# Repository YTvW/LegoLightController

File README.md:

# QBee LED Controller

A LEGO-stud-compatible LED controller board (Rev 1.0) built around the ATSAMD11C14A,
powered over USB-C. It drives up to two WS2812B (NeoPixel) strips and three
single-color LED channels.

## Hardware overview

| Part | Function |
|---|---|
| U1 — ATSAMD11C14A (SOIC-14) | MCU, 16KB flash / 4KB RAM, native USB |
| U2 — AP2111H-3.3 | 3.3V LDO for the MCU |
| P1 — USB-C (USB4110) | Power (5V) + USB 2.0 data; 5.1k CC pulldowns identify the board as a power sink |
| Q1–Q3 — BC847 | Low-side switches for the three LED channels (1k base, 10k pulldown) |
| R10, R11 — 470Ω | Series resistors on the WS2812B data lines |

### Connectors / IO

| Connector | Pads | Signal | MCU pin | Arduino pin |
|---|---|---|---|---|
| J1 | 1: +5V, 2: switched GND | LED1 channel | PA02 | 2 |
| J2 | 1: +5V, 2: switched GND | LED2 channel | PA04 | 4 |
| J3 | 1: +5V, 2: switched GND | LED3 channel | PA05 | 5 |
| J4 | 1: +5V, 2: data, 3: GND | WS2812B strip (DL1) | PA14 | 14 |
| J5 | 1: +5V, 2: data, 3: GND | WS2812B strip (DL2) | PA15 | 15 |
| J7 | 1: 3V3, 2: RESET, 3: SWCLK, 4: SWDIO, 5: NC, 6: GND | SWD programming header (DNP) | PA28/PA30/PA31 | — |
| TP1 | test point | EXT1 spare GPIO | PA08 | 8 |
| TP2 | test point | EXT2 spare GPIO | PA09 | 9 |

The LED channels (J1–J3) switch the LED's ground side through a transistor:
connect an LED (with its own series resistor if needed) between pad 1 (+5V)
and pad 2. A HIGH on the MCU pin turns the channel on.

Notes per pin:

- **PA02 (LED1, pin 2)** has no timer output — hardware PWM is not possible.
  `analogWrite()` on this pin uses the true 10-bit DAC; the transistor makes
  this behave as a crude analog dimmer only. Prefer channels LED2/LED3 for
  smooth PWM dimming.
- **PA04/PA05 (LED2/LED3)** have TC1 waveform outputs (WO0/WO1) — used by
  `pwm_driver` channels 0 and 1.
- **PA14/PA15 (strips)** also carry TC1 outputs; do not `analogWrite()` them.

## Arduino environment setup

1. Install the [Arduino IDE](https://www.arduino.cc/en/software) (2.x).
2. Add the Fab SAM core: **File → Preferences → Additional boards manager URLs**:

   ```
   https://raw.githubusercontent.com/qbolsee/ArduinoCore-fab-sam/master/json/package_Fab_SAM_index.json
   ```

3. **Tools → Board → Boards Manager**, search "Fab SAM", install
   **Fab SAM core for Arduino** (this project was built with 1.12.0).
4. Select **Tools → Board → Fab SAM boards → Generic D11C14A**.

### Board settings (Tools menu)

| Setting | Value | Notes |
|---|---|---|
| Clock Source | `INTERNAL_USB_CALIBRATED_OSCILLATOR` | Crystalless; calibrates 48MHz from USB. Switch to `INTERNAL_OSCILLATOR` if USB is disabled. |
| Bootloader Size | `4KB_BOOTLOADER` | Leaves 12KB for the application |
| Serial Config | `NO_UART_ONE_WIRE_ONE_SPI` | Saves ~1.5KB vs the default; USB `Serial` still works. The hardware UART (`Serial1`) is not wired to anything on this board. |
| USB Config | `CDC_ONLY` | Needed for `Serial` debugging and one-click uploads |
| Float | default | |
| Timer PWM Frequency | default (732.4Hz) | Only affects `analogWrite()` |

### Uploading

Normal uploads go over USB via the SAM-BA bootloader: just press Upload —
the IDE opens the port at 1200 baud to reset the board into the bootloader
automatically (this requires the running sketch to have USB CDC enabled).

If the chip is blank, or the sketch was built without CDC, flash via the SWD
pads (J7) with a CMSIS-DAP programmer and
[edbg](https://github.com/ataradov/edbg), or use the IDE's
*Burn Bootloader* with the Fab programmer selected. Once the bootloader is
on, USB uploads work as above.

## Firmware (`QBee Software/QBeeFirmware`)

| File | Purpose |
|---|---|
| `QBeeFirmware.ino` | Main sketch |
| `ws2812b_dma_driver.c/h` | WS2812B driver using **TCC0** PWM + DMA. Non-blocking: `ws2812b_show()` starts a hardware transfer and returns immediately. Uses TCC0's double-buffered `CCB` compare register so bit timing is glitch-free and immune to interrupts/USB load. |
| `pwm_driver.c/h` | LED-channel PWM using **TC1** (channels 0/1 → pins 4/5). TC2 exists but its outputs land on the SWD pins only. Costs no flash while unused (linker GC). |
| `neopixel_driver.c/h` | Older bit-banged WS2812B driver (blocks with interrupts off; superseded by the DMA driver) |

### Timer budget

| Peripheral | Owner |
|---|---|
| TCC0 | `ws2812b_dma_driver` (do not combine with `analogWrite`/`pwm_driver` on TCC0 pins) |
| TC1 | `pwm_driver` channels 0/1 (pins 4/5). Also claimed by `tone()` — don't use both. |
| TC2 | `pwm_driver` channels 2/3 — outputs only on SWD pins PA30/PA31, effectively unusable |
| SysTick | `millis()`/`micros()`/`delay()` (not a shared peripheral) |
| DMAC ch 0 | `ws2812b_dma_driver` |

### Flash budget

The app space is 12288 bytes. Measured levers if space runs out:

| Change | Approx. saving |
|---|---|
| Serial Config → `NO_UART...` | 1.5KB (free — `Serial1` unused) |
| USB Config → `WITHOUT_CDC` (drop `Serial` prints) | +2KB |
| USB Config → `USB_DISABLED` (also set Clock → `INTERNAL_OSCILLATOR`) | +4KB more |
| Bootloader → `NO_BOOTLOADER` (SWD uploads only) | +4KB of app space |

## Known hardware issues (Rev 1.0)

- **No level shifter on the WS2812B data lines.** Data is 3.3V while the
  strip runs at 5V; the strip's VIH spec is 0.7×VDD = 3.5V, so operation
  relies on real-world margin. Symptom: strips work on a USB-C wall supply
  but fail or glitch on some PC ports (slightly higher/noisier VBUS).
  Workaround: a silicon diode in series with the strip's +5V feed (drops
  strip VDD to ~4.4V). Proper fix for Rev 2: a 74AHCT1G125 / SN74LV1T125
  buffer on each data line, powered from 5V.
- **LED1 (PA02) has no hardware PWM** — see pin notes above.

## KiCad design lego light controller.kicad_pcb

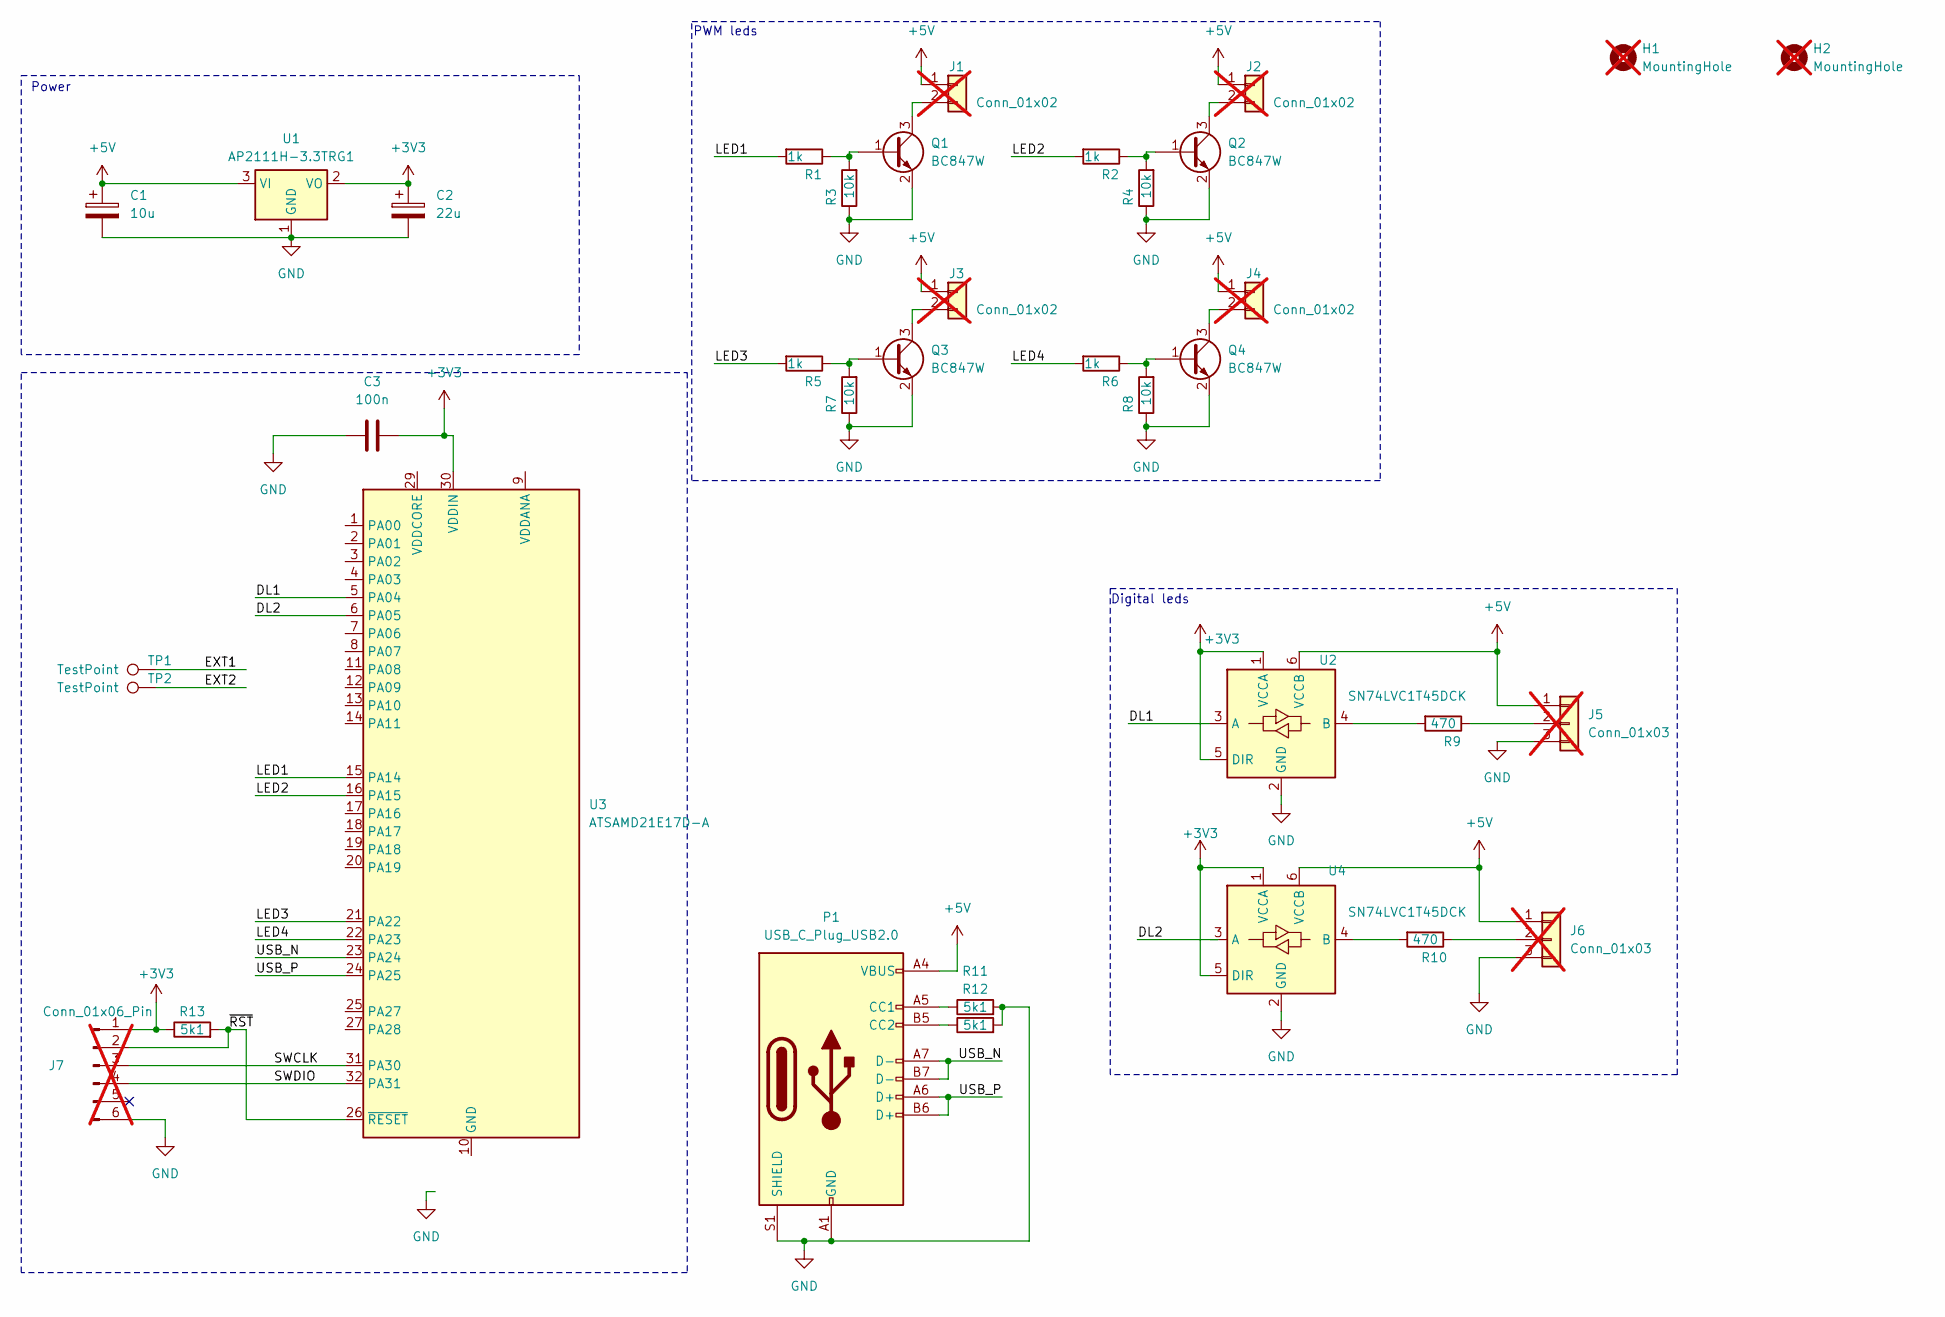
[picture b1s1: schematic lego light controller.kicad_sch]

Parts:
C1: 10u; CP_Elec_3x5.3; MPN 875105240001
C2: 22u; CP_Elec_3x5.3; MPN 875105240003
C3: 100n; C_0805_2012Metric
H1, H2: MountingHole; LEGO 4Studs; not fitted
J1, J2, J3, J4: Conn_01x02; PinHeader_1x02_P2.54mm_Vertical; not fitted
J5, J6: Conn_01x03; PinHeader_1x03_P2.54mm_Vertical; not fitted
J7: Conn_01x06_Pin; SW_DIP_SPSTx03_Slide_KingTek_DSHP03TJ_W5.25mm_P1.27mm_JPin; not fitted
P1: USB_C_Plug_USB2.0; USB_C_Receptacle_GCT_USB4110; MPN USB4110-GF-A
Q1, Q2, Q3, Q4: BC847W; SOT-23; MPN BC817-16LT3G
R1, R2, R5, R6: 1k; R_0603_1608Metric
R3, R4, R7, R8: 10k; R_0603_1608Metric
R9, R10: 470; R_0603_1608Metric
R11, R12, R13: 5k1; R_0603_1608Metric
TP1, TP2: TestPoint; TestPoint_Pad_2.0x2.0mm
U1: AP2111H-3.3TRG1; SOT-223-3_TabPin2; MPN AP2111H-3.3TRG1
U2, U4: SN74LVC1T45DCK; SOT-363_SC-70-6
U3: ATSAMD21E17D-A; TQFP-32_7x7mm_P0.8mm

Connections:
+3V3: C2.1, C3.2, J7.1, R13.1, U1.2 (VO), U2.1 (VCCA), U2.5 (DIR), U3.30 (VDDIN), U4.1 (VCCA), U4.5 (DIR)
+5V: C1.1, J1.1, J2.1, J3.1, J4.1, J5.1, J6.1, P1.A4 (VBUS), P1.A9 (VBUS), P1.B4 (VBUS), P1.B9 (VBUS), U1.3 (VI), U2.6 (VCCB), U4.6 (VCCB)
/DL1: U2.3 (A), U3.5 (PA04)
/DL2: U3.6 (PA05)
/EXT1: TP1.1 (1_1)
/EXT2: TP2.1 (1_1)
/LED1: R1.2, U3.15 (PA14)
/LED2: R2.2, U3.16 (PA15)
/LED3: R5.2, U3.21 (PA22)
/LED4: R6.2, U3.22 (PA23)
/SWCLK: J7.3, U3.31 (PA30)
/SWDIO: J7.4, U3.32 (PA31)
/USB_N: P1.A7 (D-), P1.B7 (D-), U3.23 (PA24)
/USB_P: P1.A6 (D+), P1.B6 (D+), U3.24 (PA25)
/~RST: J7.2, R13.2, U3.26 (~RESET)
GND: C1.2, C2.2, C3.1, J5.3, J6.3, J7.6, P1.A1 (GND), P1.A12 (GND), P1.B1 (GND), P1.B12 (GND), P1.S1 (SHIELD), Q1.2 (E), Q2.2 (E), Q3.2 (E), Q4.2 (E), R3.1, R4.1, R7.1, R8.1, R11.2, R12.2, U1.1 (GND), U2.2 (GND), U4.2 (GND)
unnamed: J1.2, Q1.3 (C)
unnamed: J2.2, Q2.3 (C)
unnamed: J3.2, Q3.3 (C)
unnamed: J4.2, Q4.3 (C)
unnamed: J5.2, R9.1
unnamed: J6.2, R10.1
unnamed: P1.A5 (CC1), R11.1
unnamed: P1.B5 (CC2), R12.1
unnamed: Q1.1 (B), R1.1, R3.2
unnamed: Q2.1 (B), R2.1, R4.2
unnamed: Q3.1 (B), R5.1, R7.2
unnamed: Q4.1 (B), R6.1, R8.2
unnamed: R9.2, U2.4 (B)
unnamed: U3.10 (GND), U3.28 (GND)
unnamed: R10.2, U4.4 (B)

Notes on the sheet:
Power
PWM leds
Digital leds

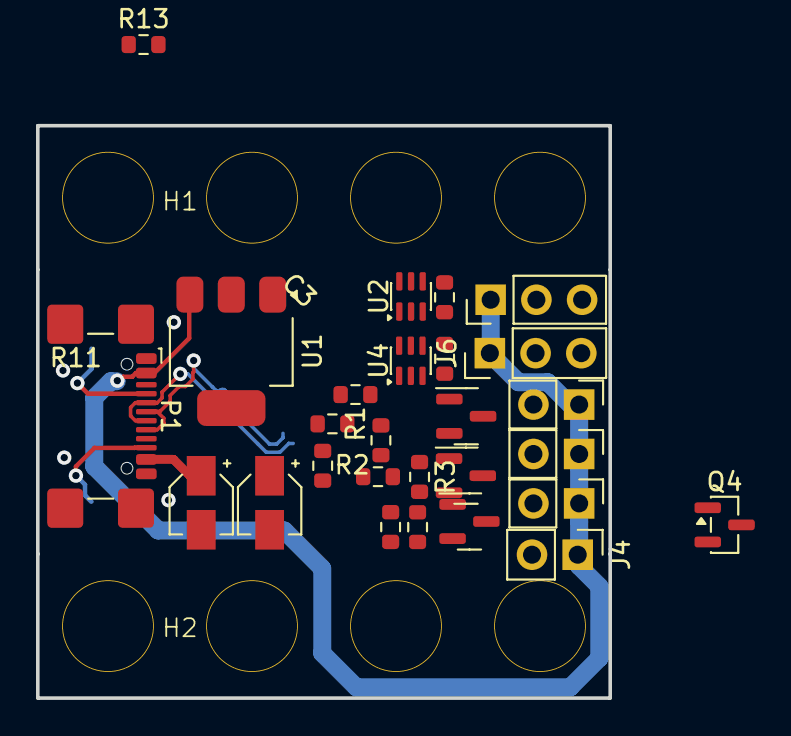
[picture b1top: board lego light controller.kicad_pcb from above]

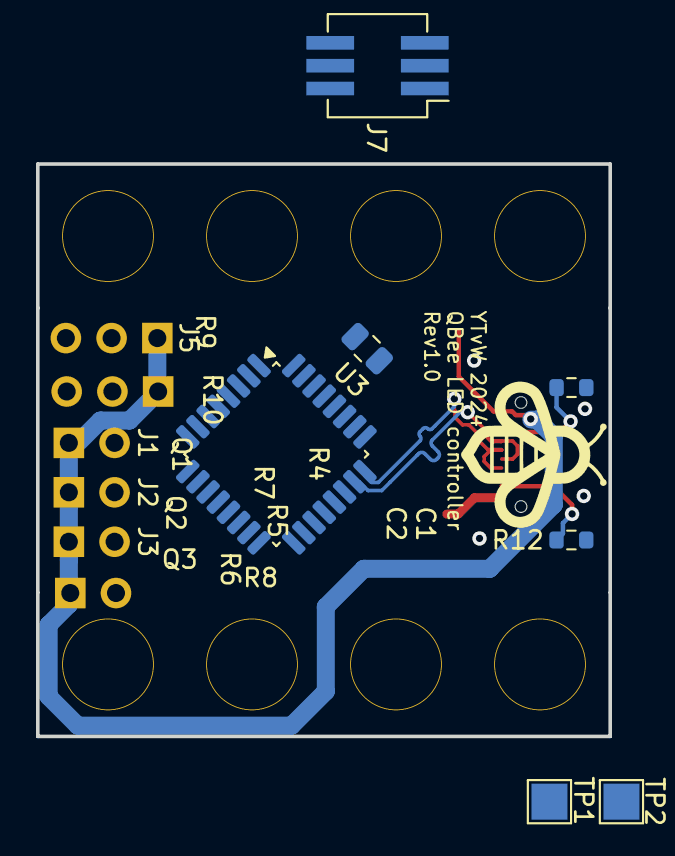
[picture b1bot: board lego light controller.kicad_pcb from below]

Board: 2 copper layers, 31.8 x 31.8 mm, 36 parts (7 on the bottom side), 28 nets.

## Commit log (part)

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2024-02-17 add progress so far
2024-02-17 make schema neat
2024-02-18 add values and update usb c
2024-02-18 update project
2024-02-19 add logo
2024-02-19 change logo size
2024-02-19 update gitignore
2024-02-19 clean up pcb
2024-02-19 fix trace to moved component
2024-02-19 fix track to 3v3 outpu
2024-02-21 update footprints and redo layout
2024-02-22 move usb to center
2024-02-22 add pads to unused io
2024-02-26 update to kicad v8
2024-02-26 fix pcb name
2024-02-26 fix BOM
2026-06-20 small fixes
